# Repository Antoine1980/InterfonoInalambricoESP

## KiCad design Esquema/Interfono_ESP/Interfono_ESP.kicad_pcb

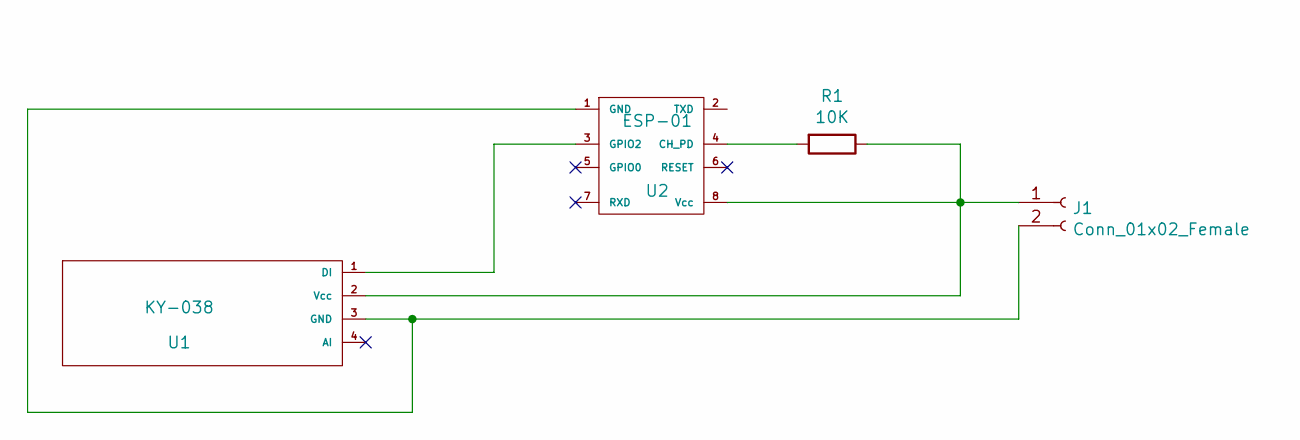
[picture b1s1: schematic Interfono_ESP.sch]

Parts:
J1: Conn_01x02_Female; JST_EH_B2B-EH-A_1x02_P2.50mm_Vertical
R1: 10K; R_Axial_DIN0204_L3.6mm_D1.6mm_P2.54mm_Vertical
U1: KY-038; PinHeader_1x04_P2.54mm_Horizontal
U2: ESP-01; PinSocket_1x04_P2.54mm_Horizontal

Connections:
unnamed: J1.1, R1.1, U1.2 (Vcc), U2.8 (Vcc)
unnamed: J1.2, U1.3 (GND), U2.1 (GND)
unnamed: R1.2, U2.4 (CH_PD)
unnamed: U1.1 (DI), U2.3 (GPIO2)

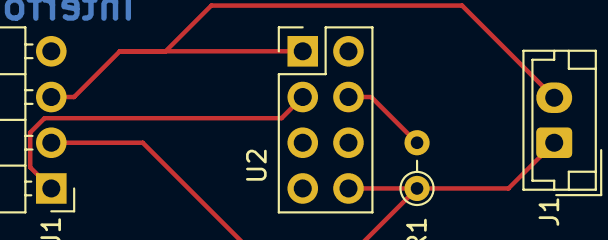
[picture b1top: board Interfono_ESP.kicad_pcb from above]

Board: 2 copper layers, 4 parts (0 on the bottom side), 4 nets.

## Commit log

2020-10-30 Pruebas
2020-11-01 SubidoProgramaVisualStudio
2020-11-01 DejarFicheroCargableESP
    Dejamos el fochero para cargar al ESP
2020-11-03 EsquemaElectrico
    Terminado esquema electrico y PCB
2020-11-11 Modelo con wifimanager
2020-11-11 WifiManager
    Implementar codigo de WifiManager
2020-11-19 WifiManager_Library
    Implememtado la libreria wifiManager
